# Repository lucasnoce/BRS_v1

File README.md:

# Basic Rocketry System

This repo will be used to develop a basic system for rocketry avionics. Development is still in initial phase, as described below, and will most definetly go under many changes and tweeks as the project evolves.

For updated project information, please refer to the [**General Requirements document**](Documentation/General_Requirements.pdf). The images and descriptions in this README may be out of date.

# Rocketry Overview
## My Background
I am a recently graduated Electronics Engineer and a space/rocketry enthusiast. For 3 years during graduation, I participated on a student rocketry team (at the time called Beyond Rocket Design, now Beyond Aerospace Department) where I helped to design and build model rockets for competitions like LASC, FBMF and so many others.

The problem is I knew nothing about rocketry back then (I still don't for the most part but hey, at least I have some xp now) and I was just starting to learn electronics, so although I knew how to code a little bit, I had never even heard of things like RTOS, threads, drivers and many many other things. Back then we used to program on Arduino IDE and created some really basic pcbs with ATmega328 and, later, ESP32 DevKit. Nothing wrong with that, we were able get somethings working, but of course my imagination never stops thinking about how much faster, reliable and efficient I could make those systems had I implemented them with some fancier techniques.

So, this is my main motivation for this project. I will be trying to implement an avionics system that does the basic but does it well. And obviously, if it works I will also try to convince the current team members to let me fly this thing on one of their rockets.

## Flight Behavior
Suborbital model rockets tend to (although, more often than desired, they don't) go through these 6 main stages during flight:
- Lift off
- Powered Ascent
- Coasting / Unpowered Ascent
- Parachute / Recovery system deployment
- Slow Descent
- Landing

<p align="center">
  <br>Flight Stages
  <br>
  <br>Source: NASA's <a href="https://www1.grc.nasa.gov/beginners-guide-to-aeronautics/flight-of-a-model-rocket/" target="_blank">Beginners Guide to Aeronautics</a>
</p>
<!--  -->

<p align="center">
  <br>Flight Stages: force analysis
  <br>
  <br>Source: Image created by the author
</p>
<!--  -->

Notice that the most important events that happen during a flight - as far as software development goes - are the transitions between stages:
- Launch: transition from being still and moving, hopefully, upwards
- Main Engine Cut-Off (MECO): transition from Powered to Unpowered Ascent
- Apogee: transition from moving upwards to downwards
- Parachute: transition from descending almost on free fall to descending slowly
- Landing: transition from descending to - we expect - softly stopping on the ground

Consider that the avionics system will have some kind of IMU (Inertial Measurement Unit), which basically tells us the instantaneous acceleration along its 3 axes. It will also feature a barometric sensor to measure the air pressure during flight. Now, let's imagine a rocket flying without any rotation, so that the Z-axis is always pointing up (this will never actually happen, but it's good for demonstration purposes). We can plot a graph with the approximate resultant acceleration (in red) and the corresponding velocity (in green) during this flight.

<p align="center">
  <br>Flight Behavior: acceleration (red) and velocity (green)
  <br>
  <br>Source: Image created by the author
</p>
<!--  -->

As we can see in this simplified example, the resultant acceleration starts at 0g (1g = 9.8 m/s^2). It rises up to about 5g and then falls back down to 0g. This period where the acceleration is positive corresponds to the powered ascent, as illustrated on the previous image. Note that the rocket hits its maximum velocity when the acceleration is 0 (of course, since a=dv/dt). Then, the vehicle experiences free fall for some time (a = -1g) until the parachutes are deployed, at around T+28 seconds. From this point, the rocket falls at a constant speed only to hit the ground at T+41 seconds.

Just to be very clear, this example is absolutely, completely inaccurate and overly simplified. In practice, the acceleration curve of the motor during powered ascent stage is much steeper and shorter and the free fall period should be significantly smaller. Also, this example ignores any kind of air resistance, which is definetely not a great idea when studying rockets. However, I hope the example helps us understand the overall behavior of a model rocket during flight.

# Project Requirements and definitions

For updated project information, please refer to the [**General Requirements document**](Documentation/General_Requirements.pdf). The images and descriptions in this README may be out of date.

## Hardware
The main objective with this project is to develop the device firmware, so hardware requirements are being defined based on components I have easy access to, mainly some off-the-shelf modules. If everything goes well after prototyping, I might review the project and design some proper hardware for it, but for now it is what it is.

## Firmware
First of all, I defined a [State Machine](Documentation/FW%20State%20Machine.png) to control the system behavior based on rockect flight phases. For this project, I considered that the parachute shall be deployed on apogee detection in order to simplify things a little. This machine will be managed by the Flight Control thread, shown in the [Architecture](Documentation/FW%20Architecture.png) structure below.

<p align="center">
  <br>FW State Machine
  <br>
  <br>Source: Image created by the author
</p>
<!--  -->

Basically, the system is initialized on the first state and, if everything is working properly, moves to S1 where the operation mode is selected based on a mechanical switch state. There are only 2 modes: UART mode is used to select secondary opModes (such as reading post-flight data and configuring the system) and Flight mode is where the magic happens.

A flight only starts after the Remove Before Flight tag is detected as removed. This has many reasons, in this case the most important being reliability, since this helps prevent a false flight start, as well as saving battery power. After that, the system has 4 detection states, one for each flight stage transition. For example, S3 keeps trying to detect lift off stage by analyzing IMU and barometric sensor data. Another example is S4, which tries to detect MECO by also analysing data from IMU and barometric sensor, or (for redundancy) can move forward after a certain timeout.

After landing has been detected (and if the rocket is still a rocket) the system tries to backup the data from internal flash to a secondary storage unit, which may be a microSD card or another flash chip (still to be defined). Finally, the system goes to S8, a state designed to facilitate rocket recovery (sometimes, they really like hiding underground) while also saving battery power. In this state, the system stays on a cycle of sleeping and waking up to beep/blink the buzzer/LEDs until the battery is critically low.

All of this is operation is illustrated in the following [Flowchart](Documentation/FW%20Flowchart.png) (also under development).

<p align="center">
  <br>FW Flowchart
  <br>
  <br>Source: Image created by the author
</p>
<!--  -->

Lastly, the system will be organized according to the following [Architecture](Documentation/FW%20Architecture.png) (yes, you guessed it, this is also not the final version).

<p align="center">
  <br>FW Architecture
  <br>
  <br>Source: Image created by the author
</p>
<!--  -->

## Tests and Validation
Untested rocket code is bad rocket code. So, I need a good way of testing this firmware to validate individual blocks and also the complete system working together. Of course, the biggest issue here is that I don't have multiple rockets to fire up and watch what happens. I am still not sure how to do this (if you have any ideas or advices, please tell me), but I fell like what I need is a combination of these 2 things:
1. Simulated flight data: a piece of code that simulates a flight by generating coherent sensor data and feeds it into the system firmware as inputs.
2. Small scale test flight: some sort of physical structure tied to my device/pdb that allows me to through it up the air and control the descent phase so that it doesn't crash onto the ground.

First method is clearly safer, but doesn't provide a "real world" condition. Second method allows me to test things in conditions closer to a real flight, but may lead to a lot of frustration, electronic waste and emptiness in my wallet. For now though, I will focus on developing the main firmware and some sort of flight simulation function.

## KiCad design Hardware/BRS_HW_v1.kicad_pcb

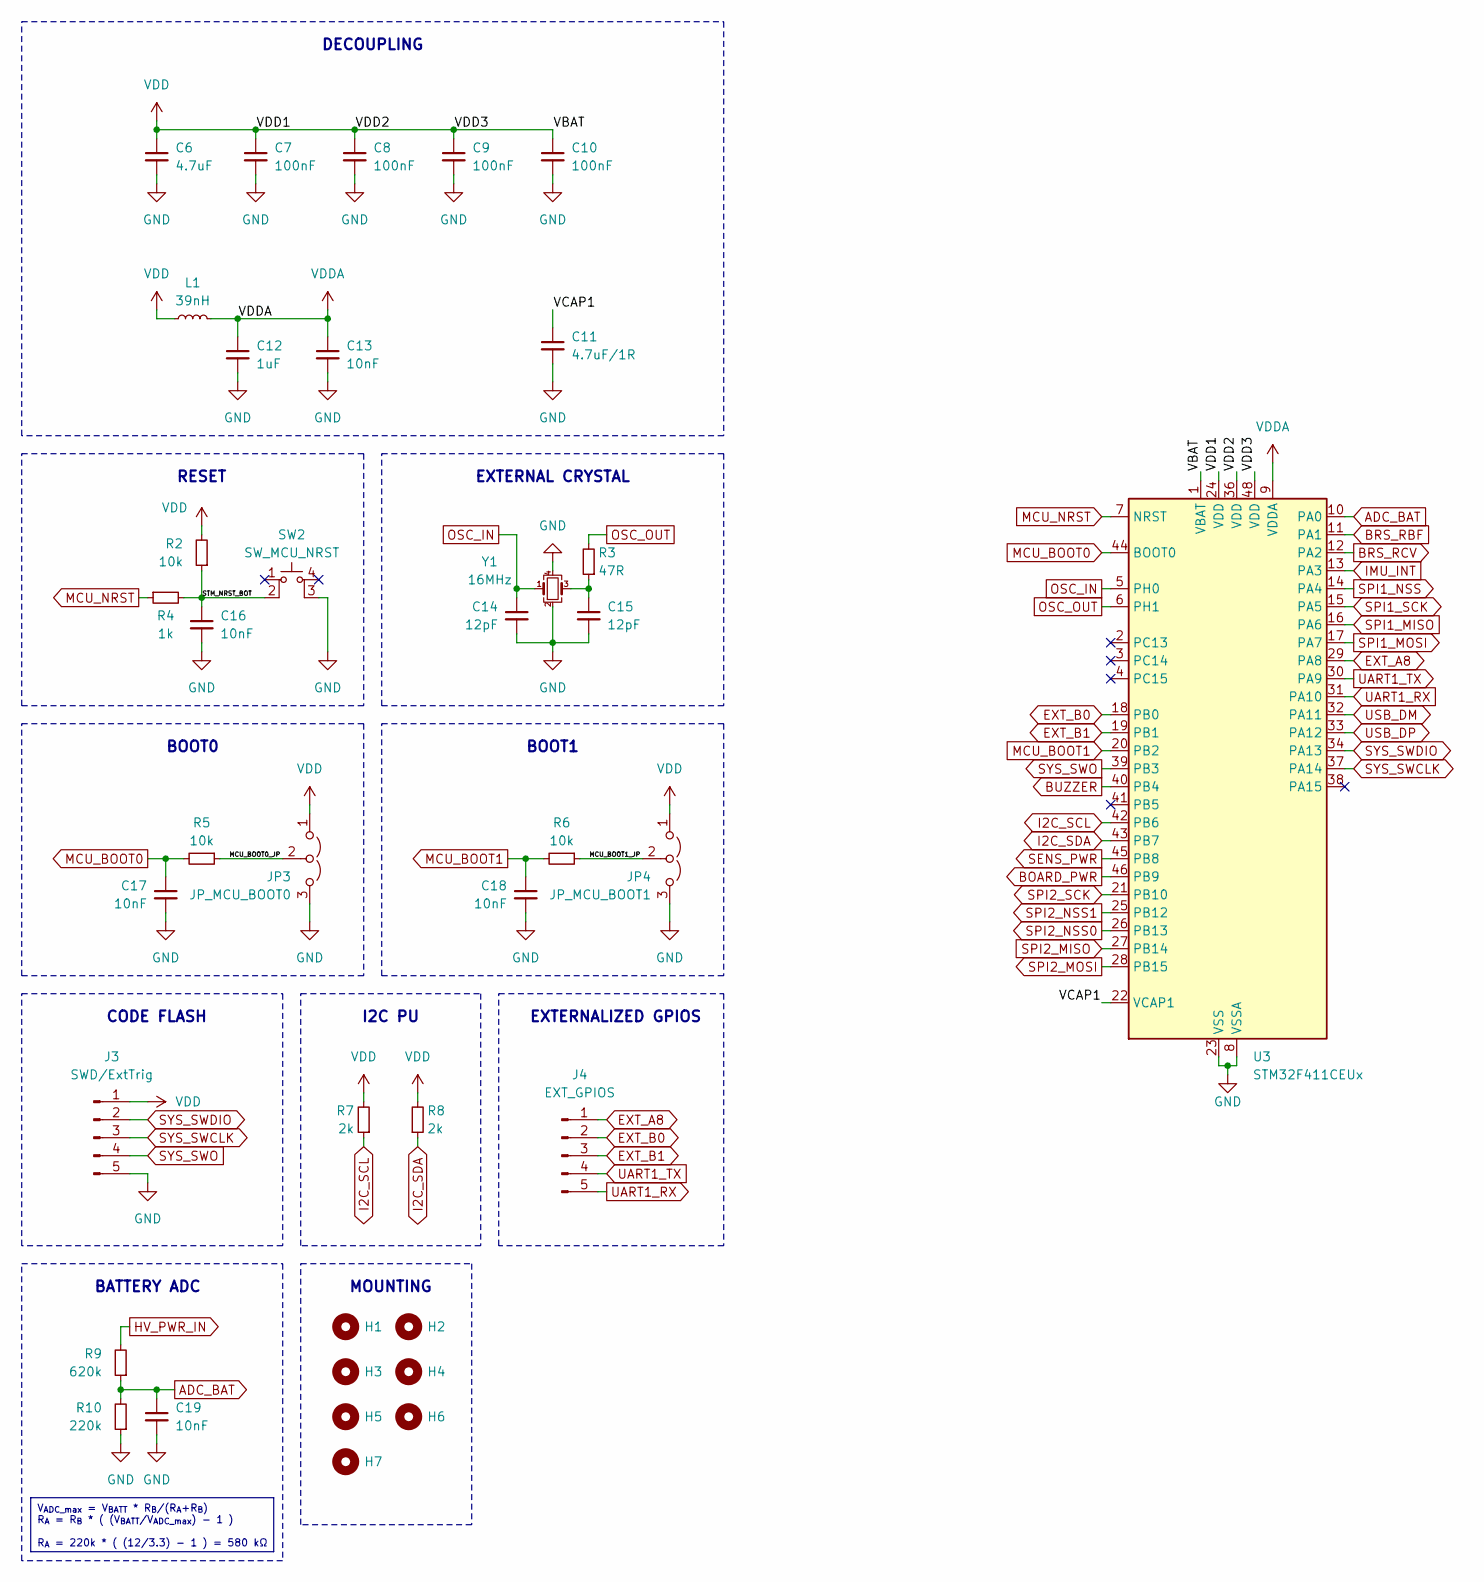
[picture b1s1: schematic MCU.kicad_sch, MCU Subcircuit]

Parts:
C6: 4.7uF; C_0603_1608Metric; LCSC Part Number C19666
C7, C8, C9, C10: 100nF; C_0402_1005Metric; LCSC Part Number C1525
C11: 4.7uF/1R; C_0603_1608Metric; LCSC Part Number C57112
C12: 1uF; C_0402_1005Metric; LCSC Part Number C52923
C13: 10nF; C_0402_1005Metric; LCSC Part Number C15195
C14, C15: 12pF; C_0402_1005Metric; LCSC Part Number C1547
C16, C17, C18, C19: 10nF; C_0603_1608Metric; LCSC Part Number C57112
H1, H3, H5, H7: SupPCB; MountingHole_2.2mm_M2_DIN965
H2, H4, H6: ToolingHole; JLCPCB_Tooling_Hole
J3: SWD/ExtTrig; PinHeader_1x05_P2.54mm_Vertical
J4: EXT_GPIOS; PinHeader_1x05_P2.54mm_Vertical
JP3: JP_MCU_BOOT0; SMD_SolderJumper_Triple_Small
JP4: JP_MCU_BOOT1; SMD_SolderJumper_Triple_Small
L1: 39nH; L_0603_1608Metric
R2, R5, R6: 10k; R_0603_1608Metric; LCSC Part Number C25804
R3: 47R; R_0402_1005Metric; LCSC Part Number C25120
R4: 1k; R_0603_1608Metric; LCSC Part Number C21190
R7, R8: 2k; R_0402_1005Metric; LCSC Part Number C22975
R9: 620k; R_0603_1608Metric; LCSC Part Number C22975
R10: 220k; R_0603_1608Metric; LCSC Part Number C22975
SW2: SW_MCU_NRST; SW_TS-1187A-B-A-B; LCSC C318884
U3: STM32F411CEUx; QFN-48-1EP_7x7mm_P0.5mm_EP5.6x5.6mm
Y1: 16MHz; Crystal_SMD_Abracon_ABM8G-4Pin_3.2x2.5mm; LCSC Part Number C13738

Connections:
/MCU/MCU_BOOT0_JP: JP3.2 (C), R5.1
/MCU/MCU_BOOT1_JP: JP4.2 (C), R6.1
/MCU/STM_NRST_BOT: C16.1, R2.1, R4.2, SW2.2
/MCU/VCAP1: C11.1, U3.22 (VCAP1)
ADC_BAT: C19.1, R9.1, R10.2, U3.10 (PA0)
BOARD_PWR: U3.46 (PB9); also elsewhere on the board
BRS_RBF: U3.11 (PA1); also elsewhere on the board
BRS_RCV: U3.12 (PA2); also elsewhere on the board
BUZZER: U3.40 (PB4); also elsewhere on the board
EXT_A8: J4.1, U3.29 (PA8)
EXT_B0: J4.2, U3.18 (PB0)
EXT_B1: J4.3, U3.19 (PB1)
GND: C6.2, C7.2, C8.2, C9.2, C10.2, C11.2, C12.2, C13.2, C14.2, C15.2, C16.2, C17.2, C18.2, C19.2, J3.5, JP3.3 (B), JP4.3 (B), R10.1, SW2.3 (K), U3.8 (VSSA), U3.23 (VSS), U3.35 (VSS), U3.47 (VSS), U3.49 (VSS), Y1.2, Y1.4; also elsewhere on the board
HV_PWR_IN: R9.2; also elsewhere on the board
I2C_SCL: R7.1, U3.42 (PB6); also elsewhere on the board
I2C_SDA: R8.1, U3.43 (PB7); also elsewhere on the board
IMU_INT: U3.13 (PA3); also elsewhere on the board
MCU_BOOT0: C17.1, R5.2, U3.44 (BOOT0)
MCU_BOOT1: C18.1, R6.2, U3.20 (PB2)
MCU_NRST: R4.1, U3.7 (NRST)
unnamed: C15.1, R3.1, Y1.3
OSC_IN: C14.1, U3.5 (PH0), Y1.1
OSC_OUT: R3.2, U3.6 (PH1)
SENS_PWR: U3.45 (PB8); also elsewhere on the board
SPI1_MISO: U3.16 (PA6); also elsewhere on the board
SPI1_MOSI: U3.17 (PA7); also elsewhere on the board
SPI1_NSS: U3.14 (PA4); also elsewhere on the board
SPI1_SCK: U3.15 (PA5); also elsewhere on the board
SPI2_MISO: U3.27 (PB14); also elsewhere on the board
SPI2_MOSI: U3.28 (PB15); also elsewhere on the board
SPI2_NSS0: U3.26 (PB13); also elsewhere on the board
SPI2_NSS1: U3.25 (PB12); also elsewhere on the board
SPI2_SCK: U3.21 (PB10); also elsewhere on the board
SYS_SWCLK: J3.3, U3.37 (PA14)
SYS_SWDIO: J3.2, U3.34 (PA13)
SYS_SWO: J3.4, U3.39 (PB3)
UART1_RX: J4.5, U3.31 (PA10)
UART1_TX: J4.4, U3.30 (PA9)
USB_DM: U3.32 (PA11); also elsewhere on the board
USB_DP: U3.33 (PA12); also elsewhere on the board
VDD: C6.1, C7.1, C8.1, C9.1, C10.1, J3.1, JP3.1 (A), JP4.1 (A), L1.1, R2.2, R7.2, R8.2, U3.1 (VBAT), U3.24 (VDD), U3.36 (VDD), U3.48 (VDD); also elsewhere on the board
VDDA: C12.1, C13.1, L1.2, U3.9 (VDDA)

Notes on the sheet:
V_{ADC_max} = V_{BATT} * R_{B}/(R_{A}+R_{B}) R_{A} = R_{B} * ( (V_{BATT}/V_{ADC_max}) - 1 ) R_{A} = 220k * ( (12/3.3) - 1 ) = 580 kΩ
BOOT1
MOUNTING
CODE FLASH
EXTERNAL CRYSTAL
I2C PU
DECOUPLING
BOOT0
EXTERNALIZED GPIOS
BATTERY ADC
RESET

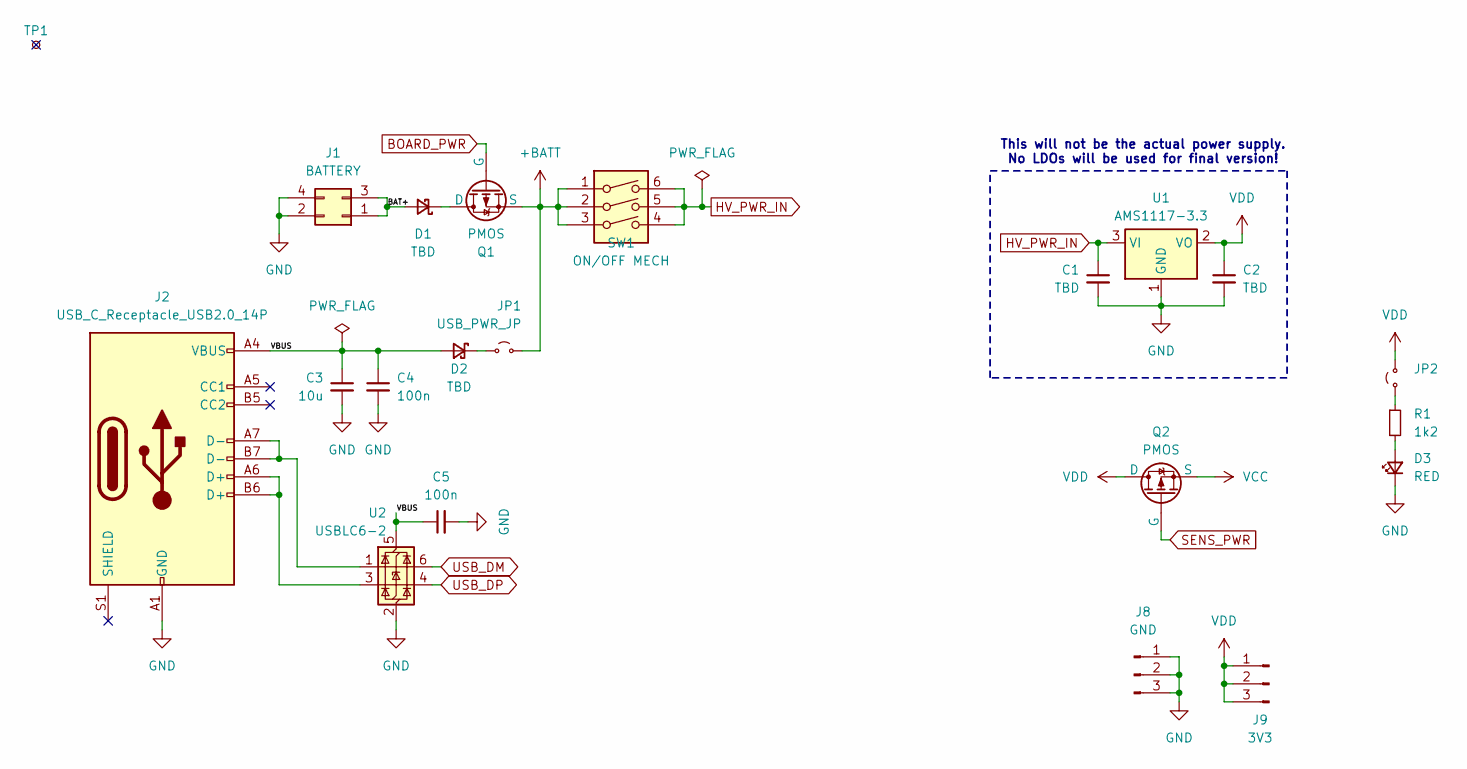
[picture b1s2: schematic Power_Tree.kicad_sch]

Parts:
C1, C2: TBD; C_0603_1608Metric
C3: 10u; C_0603_1608Metric
C4, C5: 100n; C_0603_1608Metric
D1, D2: TBD; D_SOD-123
D3: RED; LED_0603_1608Metric
J1: BATTERY; Molex_Micro-Fit_3.0_43045-0412_2x02_P3.00mm_Vertical
J2: USB_C_Receptacle_USB2.0_14P; USB_C_Receptacle_GCT_USB4105-xx-A_16P_TopMnt_Horizontal
J8: GND; PinHeader_1x03_P2.54mm_Vertical
J9: 3V3; PinHeader_1x03_P2.54mm_Vertical
JP1: USB_PWR_JP; SolderJumper-2_P1.3mm_Open_RoundedPad1.0x1.5mm
JP2: Jumper_2_Small_Open; SolderJumper-2_P1.3mm_Open_RoundedPad1.0x1.5mm
Q1, Q2: PMOS; SOT-23
R1: 1k2; R_0603_1608Metric
SW1: ON/OFF MECH; SW_DIP_SPSTx03_Slide_6.7x9.18mm_W7.62mm_P2.54mm_LowProfile
TP1: TestPoint_Small; TestPoint_Pad_D1.5mm
U1: AMS1117-3.3; SOT-223-3_TabPin2
U2: USBLC6-2; SOT-23-6

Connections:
+BATT: JP1.2 (B), Q1.3 (S), SW1.1, SW1.2, SW1.3
/Power_Tree/BAT+: D1.2 (A), J1.1, J1.3
/Power_Tree/VBUS: C3.1, C4.1, C5.1, D2.2 (A), J2.A4 (VBUS), J2.A9 (VBUS), J2.B4 (VBUS), J2.B9 (VBUS), U2.5 (VBUS)
BOARD_PWR: Q1.2 (G); also elsewhere on the board
GND: C1.2, C2.2, C3.2, C4.2, C5.2, D3.1 (K), J1.2, J1.4, J2.A1 (GND), J2.A12 (GND), J2.B1 (GND), J2.B12 (GND), J8.1, J8.2, J8.3, U1.1 (GND), U2.2 (GND); also elsewhere on the board
HV_PWR_IN: C1.1, SW1.4, SW1.5, SW1.6, U1.3 (VI); also elsewhere on the board
unnamed: D1.1 (K), Q1.1 (D)
unnamed: D2.1 (K), JP1.1 (A)
unnamed: D3.2 (A), R1.2
unnamed: J2.A6 (D+), J2.B6 (D+), U2.3 (I/O2)
unnamed: J2.A7 (D-), J2.B7 (D-), U2.1 (I/O1)
unnamed: JP2.1 (A), R1.1
SENS_PWR: Q2.2 (G); also elsewhere on the board
USB_DM: U2.6 (I/O1); also elsewhere on the board
USB_DP: U2.4 (I/O2); also elsewhere on the board
VCC: Q2.3 (S); also elsewhere on the board
VDD: C2.1, J9.1, J9.2, J9.3, JP2.2 (B), Q2.1 (D), U1.2 (VO); also elsewhere on the board

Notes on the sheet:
This will not be the actual power supply. No LDOs will be used for final version!

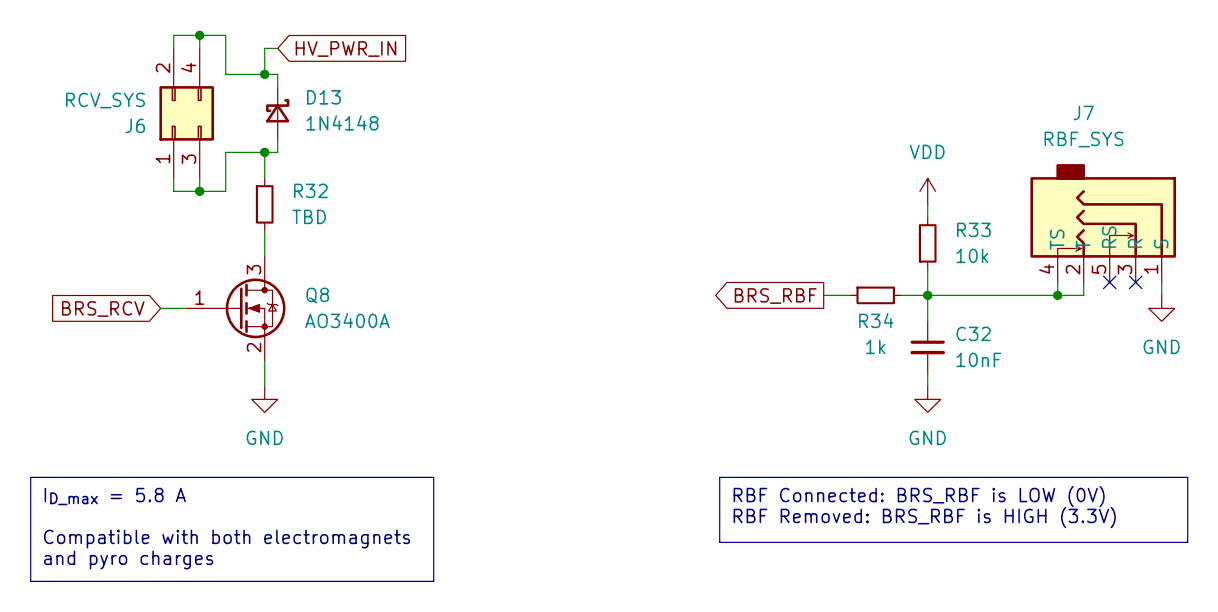
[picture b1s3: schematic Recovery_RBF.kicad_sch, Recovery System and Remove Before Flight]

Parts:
C32: 10nF; C_0603_1608Metric; LCSC Part Number C57112
D13: 1N4148; D_SOD-123
J6: RCV_SYS; Molex_Micro-Fit_3.0_43045-0412_2x02_P3.00mm_Vertical
J7: RBF_SYS; AudioJack_Vertical
Q8: AO3400A; SOT-23
R32: TBD; R_0603_1608Metric
R33: 10k; R_0603_1608Metric; LCSC Part Number C25804
R34: 1k; R_0603_1608Metric; LCSC Part Number C21190

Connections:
BRS_RBF: R34.1; also elsewhere on the board
BRS_RCV: Q8.1 (G); also elsewhere on the board
GND: C32.2, J7.1 (S), Q8.2 (S); also elsewhere on the board
HV_PWR_IN: D13.1 (K), J6.2, J6.4; also elsewhere on the board
unnamed: D13.2 (A), J6.1, J6.3, R32.1
unnamed: C32.1, J7.2 (T), J7.4 (TS), R33.1, R34.2
unnamed: Q8.3 (D), R32.2
VDD: R33.2; also elsewhere on the board

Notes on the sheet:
RBF Connected: BRS_RBF is LOW (0V) RBF Removed: BRS_RBF is HIGH (3.3V)
I_{D_max} = 5.8 A Compatible with both electromagnets and pyro charges

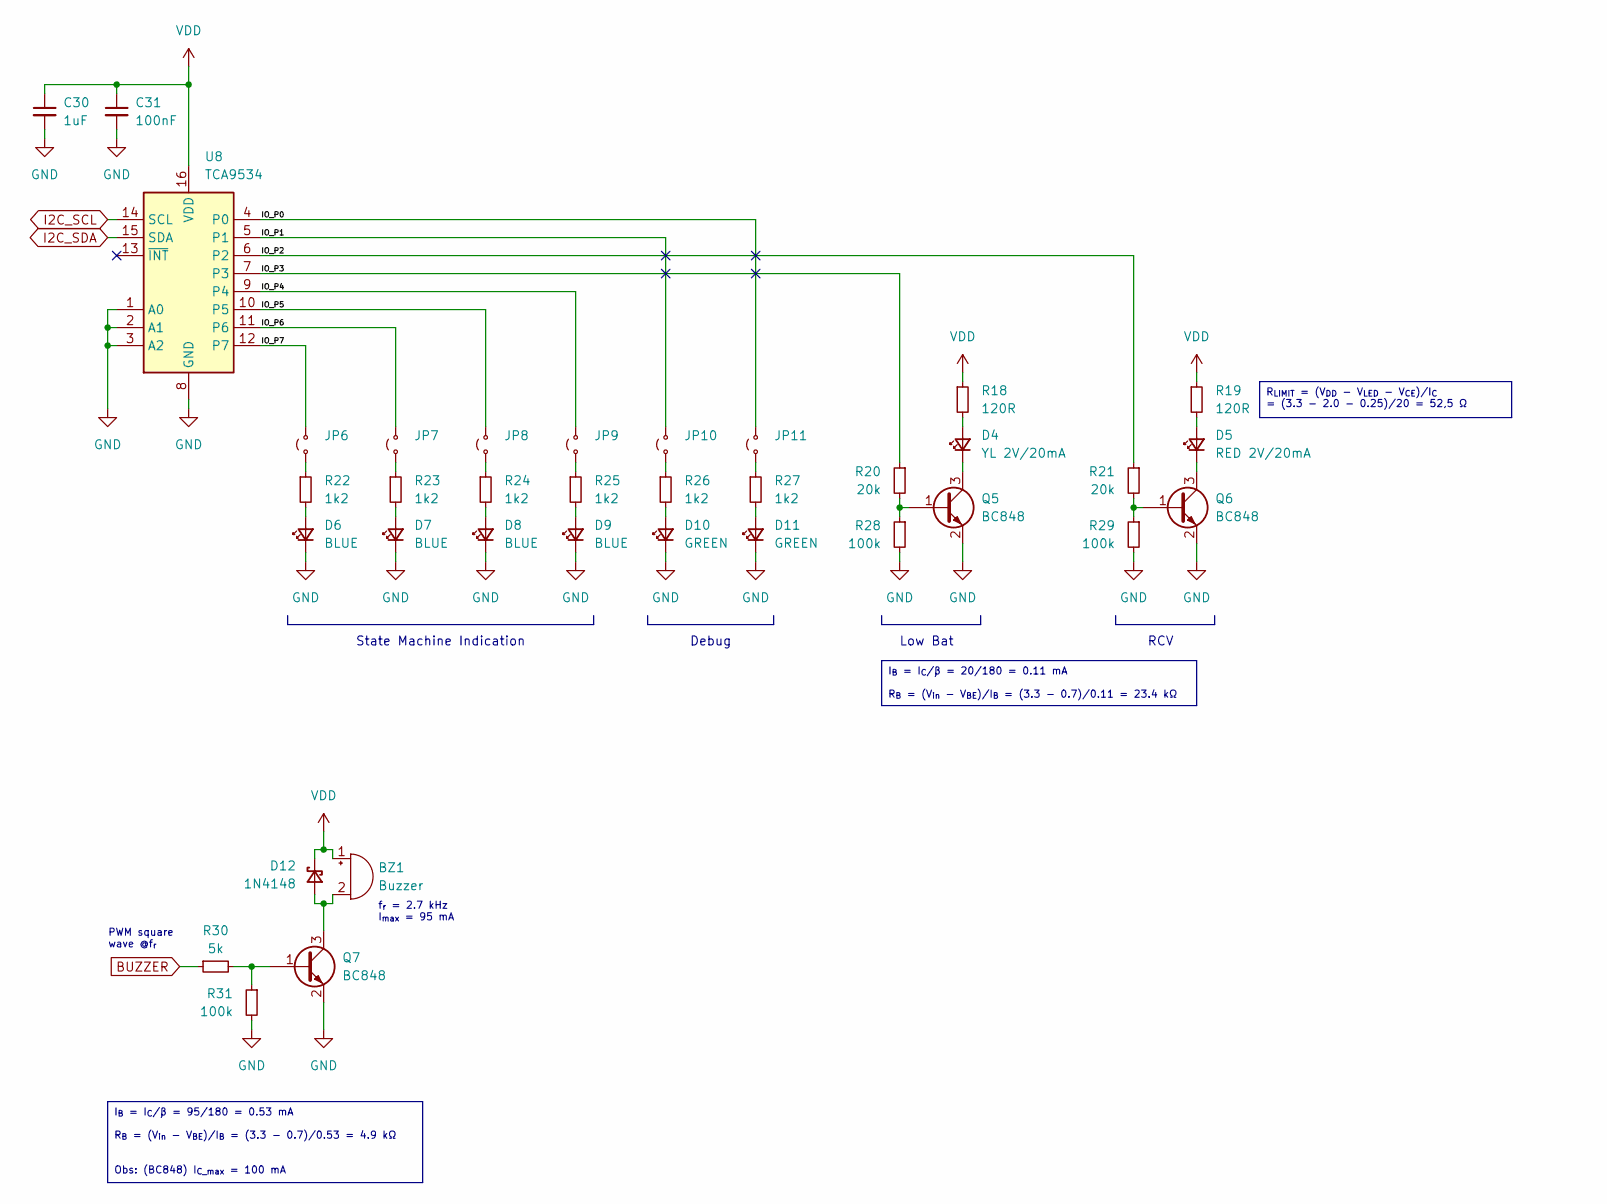
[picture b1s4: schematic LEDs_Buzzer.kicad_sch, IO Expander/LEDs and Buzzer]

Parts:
BZ1: Buzzer; PUIAudio_SMT_0825_S_4_R
C30: 1uF; C_0603_1608Metric; LCSC Part Number C57112
C31: 100nF; C_0603_1608Metric; LCSC Part Number C57112
D4: YL 2V/20mA; LED_0805_2012Metric
D5: RED 2V/20mA; LED_0805_2012Metric
D6, D7, D8, D9: BLUE; LED_0603_1608Metric
D10, D11: GREEN; LED_0603_1608Metric
D12: 1N4148; D_SOD-123
JP6, JP7, JP8, JP9, JP10, JP11: Jumper_2_Small_Open; SMD_SolderJumper_Small
Q5, Q6, Q7: BC848; SOT-23
R18, R19: 120R; R_0603_1608Metric
R20, R21: 20k; R_0603_1608Metric
R22, R23, R24, R25, R26, R27: 1k2; R_0603_1608Metric
R28, R29, R31: 100k; R_0603_1608Metric
R30: 5k; R_0603_1608Metric
U8: TCA9534; TSSOP-16_4.4x5mm_P0.65mm

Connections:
/Peripherals/LEDs_Buzzer/IO_P0: JP11.2 (B), U8.4 (P0)
/Peripherals/LEDs_Buzzer/IO_P1: JP10.2 (B), U8.5 (P1)
/Peripherals/LEDs_Buzzer/IO_P2: R21.1, U8.6 (P2)
/Peripherals/LEDs_Buzzer/IO_P3: R20.1, U8.7 (P3)
/Peripherals/LEDs_Buzzer/IO_P4: JP9.2 (B), U8.9 (P4)
/Peripherals/LEDs_Buzzer/IO_P5: JP8.2 (B), U8.10 (P5)
/Peripherals/LEDs_Buzzer/IO_P6: JP7.2 (B), U8.11 (P6)
/Peripherals/LEDs_Buzzer/IO_P7: JP6.2 (B), U8.12 (P7)
BUZZER: R30.1; also elsewhere on the board
GND: C30.2, C31.2, D6.1 (K), D7.1 (K), D8.1 (K), D9.1 (K), D10.1 (K), D11.1 (K), Q5.2 (E), Q6.2 (E), Q7.2 (E), R28.2, R29.2, R31.2, U8.1 (A0), U8.2 (A1), U8.3 (A2), U8.8 (GND); also elsewhere on the board
I2C_SCL: U8.14 (SCL); also elsewhere on the board
I2C_SDA: U8.15 (SDA); also elsewhere on the board
unnamed: BZ1.2 (-), D12.2 (A), Q7.3 (C)
unnamed: D4.2 (A), R18.2
unnamed: D4.1 (K), Q5.3 (C)
unnamed: D5.2 (A), R19.2
unnamed: D5.1 (K), Q6.3 (C)
unnamed: D6.2 (A), R22.2
unnamed: D7.2 (A), R23.2
unnamed: D8.2 (A), R24.2
unnamed: D9.2 (A), R25.2
unnamed: D10.2 (A), R26.2
unnamed: D11.2 (A), R27.2
unnamed: JP6.1 (A), R22.1
unnamed: JP7.1 (A), R23.1
unnamed: JP8.1 (A), R24.1
unnamed: JP9.1 (A), R25.1
unnamed: JP10.1 (A), R26.1
unnamed: JP11.1 (A), R27.1
unnamed: Q5.1 (B), R20.2, R28.1
unnamed: Q6.1 (B), R21.2, R29.1
unnamed: Q7.1 (B), R30.2, R31.1
VDD: BZ1.1 (+), C30.1, C31.1, D12.1 (K), R18.1, R19.1, U8.16 (VDD); also elsewhere on the board

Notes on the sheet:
R_{LIMIT} = (V_{DD} - V_{LED} - V_{CE})/I_{C} = (3.3 - 2.0 - 0.25)/20 = 52,5 Ω
I_{B} = I_{C}/β = 95/180 = 0.53 mA R_{B} = (V_{in} - V_{BE})/I_{B} = (3.3 - 0.7)/0.53 = 4.9 kΩ Obs: (BC848) I_{C_max} = 100 mA
I_{B} = I_{C}/β = 20/180 = 0.11 mA R_{B} = (V_{in} - V_{BE})/I_{B} = (3.3 - 0.7)/0.11 = 23.4 kΩ
Low Bat
PWM square wave @f_{r}
f_{r} = 2.7 kHz I_{max} = 95 mA
State Machine Indication
Debug
RCV

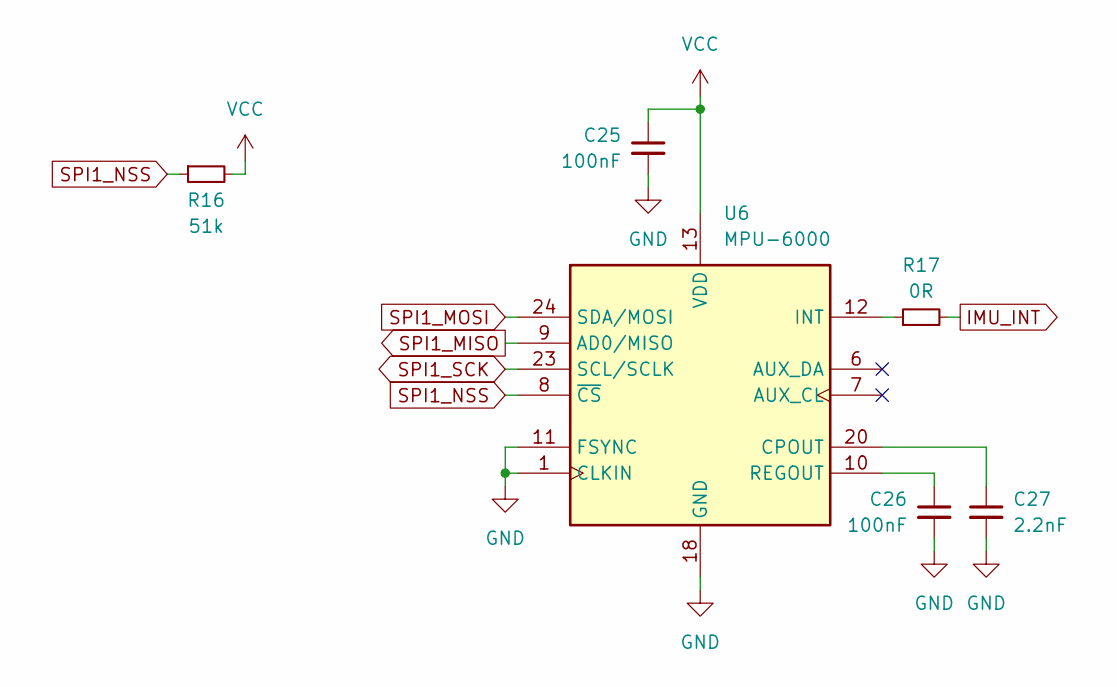
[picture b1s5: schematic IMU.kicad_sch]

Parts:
C25, C26: 100nF; C_0603_1608Metric; LCSC Part Number C57112
C27: 2.2nF; C_0603_1608Metric; LCSC Part Number C57112
R16: 51k; R_0603_1608Metric
R17: 0R; R_0603_1608Metric
U6: MPU-6000; InvenSense_QFN-24_4x4mm_P0.5mm

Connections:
GND: C25.2, C26.2, C27.2, U6.1 (CLKIN), U6.11 (FSYNC), U6.18 (GND); also elsewhere on the board
IMU_INT: R17.2; also elsewhere on the board
unnamed: C27.1, U6.20 (CPOUT)
unnamed: R17.1, U6.12 (INT)
unnamed: C26.1, U6.10 (REGOUT)
SPI1_MISO: U6.9 (AD0/MISO); also elsewhere on the board
SPI1_MOSI: U6.24 (SDA/MOSI); also elsewhere on the board
SPI1_NSS: R16.1, U6.8 (~CS); also elsewhere on the board
SPI1_SCK: U6.23 (SCL/SCLK); also elsewhere on the board
VCC: C25.1, R16.2, U6.13 (VDD); also elsewhere on the board

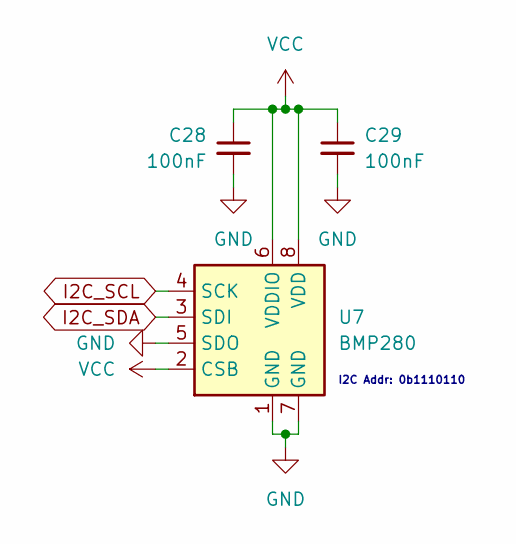
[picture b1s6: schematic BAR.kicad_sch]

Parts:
C28, C29: 100nF; C_0402_1005Metric; LCSC Part Number C57112
U7: BMP280; Bosch_LGA-8_2x2.5mm_P0.65mm_ClockwisePinNumbering

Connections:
GND: C28.2, C29.2, U7.1 (GND), U7.5 (SDO), U7.7 (GND); also elsewhere on the board
I2C_SCL: U7.4 (SCK); also elsewhere on the board
I2C_SDA: U7.3 (SDI); also elsewhere on the board
VCC: C28.1, C29.1, U7.2 (CSB), U7.6 (VDDIO), U7.8 (VDD); also elsewhere on the board

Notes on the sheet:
I2C Addr: 0b1110110

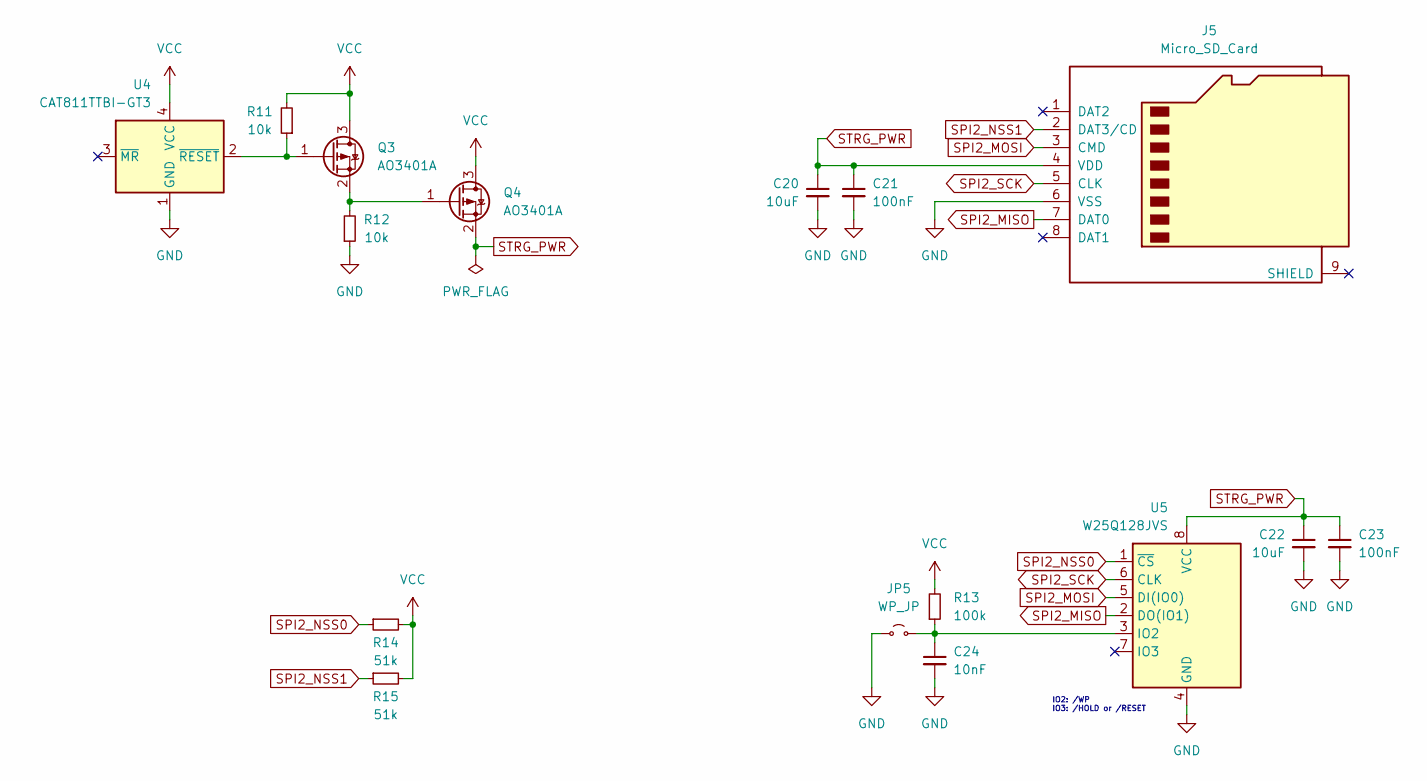
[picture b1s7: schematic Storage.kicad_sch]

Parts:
C20, C22: 10uF; C_0603_1608Metric; LCSC Part Number C57112
C21, C23: 100nF; C_0603_1608Metric; LCSC Part Number C57112
C24: 10nF; C_0603_1608Metric; LCSC Part Number C57112
J5: Micro_SD_Card; microSD_HC_Wuerth_693072010801
JP5: WP_JP; SolderJumper-2_P1.3mm_Open_RoundedPad1.0x1.5mm
Q3, Q4: AO3401A; SOT-23
R11, R12: 10k; R_0603_1608Metric
R13: 100k; R_0603_1608Metric
R14, R15: 51k; R_0603_1608Metric
U4: CAT811TTBI-GT3; SOT-143
U5: W25Q128JVS; SOIC-8_5.23x5.23mm_P1.27mm

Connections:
GND: C20.2, C21.2, C22.2, C23.2, C24.2, J5.6 (VSS), JP5.1 (A), R12.1, U4.1 (GND), U5.4 (GND); also elsewhere on the board
unnamed: C24.1, JP5.2 (B), R13.1, U5.3 (IO2)
unnamed: Q3.1 (G), R11.1, U4.2 (~RESET)
unnamed: Q3.2 (S), Q4.1 (G), R12.2
SPI2_MISO: J5.7 (DAT0), U5.2 (DO(IO1)); also elsewhere on the board
SPI2_MOSI: J5.3 (CMD), U5.5 (DI(IO0)); also elsewhere on the board
SPI2_NSS0: R14.1, U5.1 (~CS); also elsewhere on the board
SPI2_NSS1: J5.2 (DAT3/CD), R15.1; also elsewhere on the board
SPI2_SCK: J5.5 (CLK), U5.6 (CLK); also elsewhere on the board
STRG_PWR: C20.1, C21.1, C22.1, C23.1, J5.4 (VDD), Q4.2 (S), U5.8 (VCC)
VCC: Q3.3 (D), Q4.3 (D), R11.2, R13.2, R14.2, R15.2, U4.4 (VCC); also elsewhere on the board

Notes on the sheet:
IO2: /WP IO3: /HOLD or /RESET

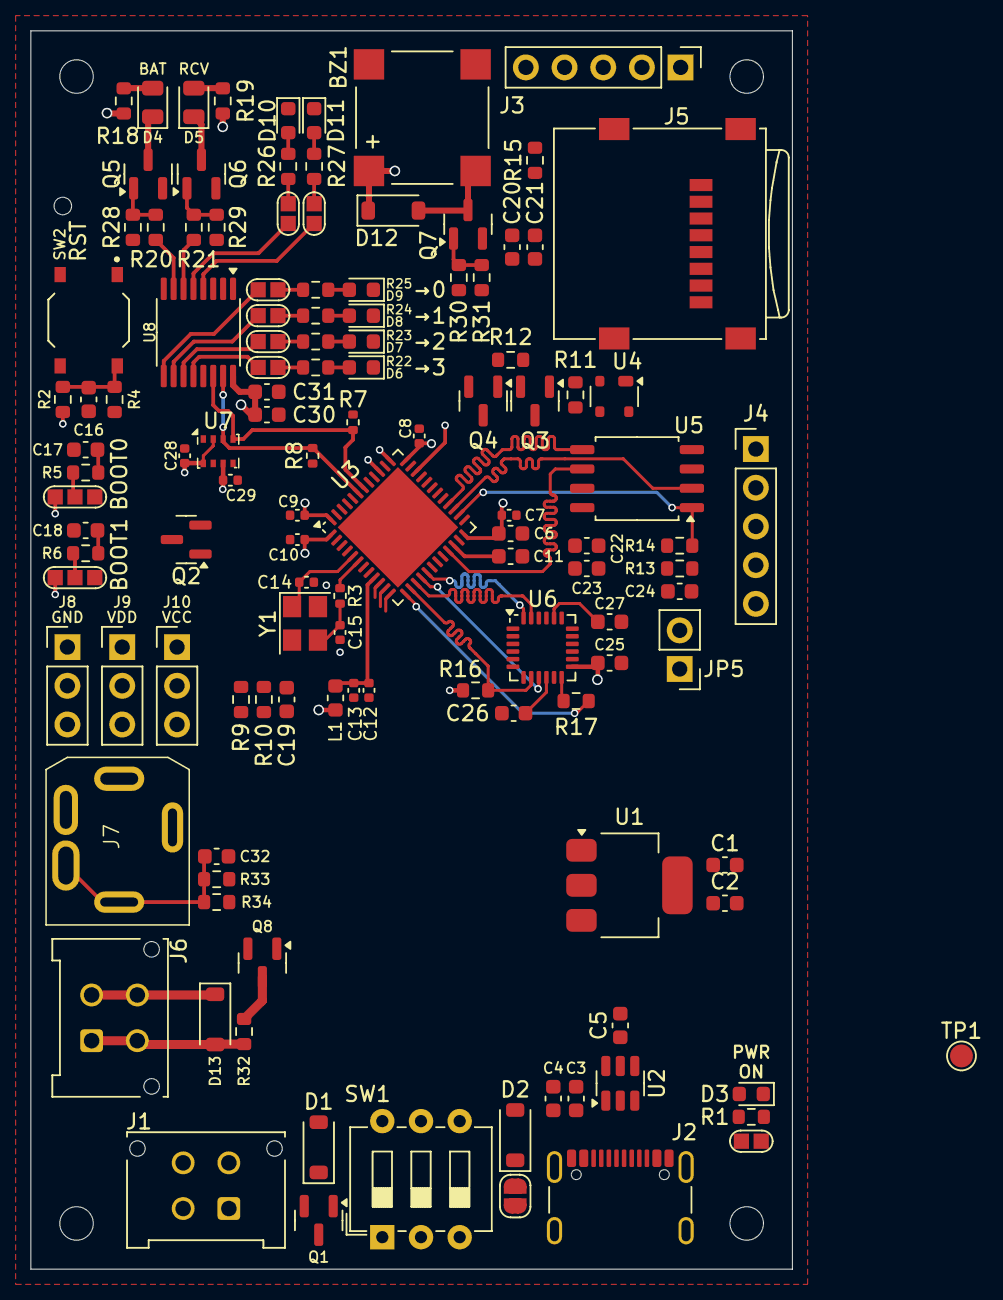
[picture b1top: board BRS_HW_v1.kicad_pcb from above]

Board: 6 copper layers, 50.0 x 81.3 mm, 129 parts (0 on the bottom side), 90 nets.

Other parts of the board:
J10: VCC; PinHeader_1x03_P2.54mm_Vertical

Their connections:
VCC: J10.1, J10.2, J10.3; also elsewhere on the board

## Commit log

2025-01-30 Writing README.md
2025-02-03 Updating README
2025-02-03 Add images to README.md
2025-02-04 Adding General Requirements Document, still unfinished
2025-02-05 Add gitignore file
2025-02-05 Adding stm32 project files
2025-02-05 Updating CMakeLists.txt
2025-02-05 Moved stm32 project into repo root folder
2025-02-05 Create Documentation folder and moved pdf
2025-02-05 Implementing IO Expander driver
2025-02-06 Implemented IO Expander driver
2025-02-07 Adding bsp layer
2025-02-07 Sync with modules/bsp
2025-02-07 Integrated with bsp
2025-02-07 Update General Requirements pdf
2025-02-07 Update Documentation
2025-02-11 Update README and Requirements
2025-02-11 Adding HW Block Diagram.png
2025-02-13 Sync with main
2025-02-13 Restructuring
2025-02-13 Adding HW design
2025-02-13 Developing HW
2025-02-14 Developing HW - routing
2025-05-22 HW modifications
2025-05-22 Removing old FW files
2025-05-22 Project restructure
2025-05-22 Removing old SW project files
2025-05-22 First dev commit
2025-05-24 Fixed compile path
2025-05-29 Implemented bsp_timers to support led blink
2025-05-29 Implemented bsp_brs to unify bsp control
2025-05-29 Continued leds implementation
2025-05-29 Implemented timer callback
2025-05-29 Adding io expander simulation
2025-05-29 Adding README to breadboard tests
2025-06-07 Trying to get test to work, still not there yet
2025-06-18 Working on power source
